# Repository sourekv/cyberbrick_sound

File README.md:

# cyberbrick_sound

Engine sound module for Bambu Lab CyberBrick RC models (first target: the truck). A small board hangs on one servo
cable from the CyberBrick receiver, gets all transmitter channels from it as serial data, and plays an engine sound
through an I2S amplifier and a speaker: idle, rpm following the throttle, a virtual gearbox, ignition with starter,
engine stop and horn. It never touches the original signal path: if the module fails, the model still drives.

**Web app for the sound sets (Chrome or Edge): https://sourekv.github.io/cyberbrick_sound/**

**Documentation, grouped by what you want to do: [`docs/README.md`](docs/README.md)**

## Status

State of 2026-11-26; what is still open: `docs/roadmap.md`.

- **The shield board works** (2026-11-21): the first assembled rev A board with a Waveshare ESP32-S3-Zero-N8R8-M and
  the firmware `engine_sets`; USB and the receiver may be connected at the same time.
- **Sound sets**: seven default sets on the module, and a web app that tests, writes and renames them, sets the volume
  and updates the firmware, over USB or Bluetooth (2026-11-22).
- **Prototype** on a breadboard in the truck before it: MAX98357A module, 40 mm 4 Ohm speaker
  in a printed 30 ml sealed box, with a speaker EQ tuned for the box (2026-11-07).
- **Channel data link works** (2026-11-06): about 27 frames per second, no checksum errors; ignition, starter,
  stop and horn from the transmitter.
- **Gearbox effects** (2026-11-08): a shift sound on every upshift; reverse is detected from the stick and does not
  shift.
- **Shield PCB**: KiCad schematic, routed board and assembly files for JLCPCB and PCBWay exist (`hardware/shield/`);
  reviewed in KiCad by a colleague of the owner on 2026-11-12 (no remarks), quoted by both services, ordered at JLCPCB on 2026-11-13 (5 assembled boards), production file and parts placement confirmed on 2026-11-14, delivered on 2026-11-20 at 12:14 (photo of the five boards: SMD parts fitted, J1/J3/J4 not yet soldered; the owner calls them "rev. 0", in the repository they are rev A).
- Which engine sound to use is the user's choice: the seven candidates became the default sets (2026-11-14).

## How it works

```
transmitter --radio--> receiver in the model --S4 servo header (S, V, G)--> sound module
```

| Where | What we added |
|---|---|
| Transmitter (CyberBrick Remote Control Transmitter Shield - XA003 XA005) | in the configuration only: the event that starts the receiver snippet by itself after power-up (moved centre of L2), and a long press of the L Shoulder Button to restart it |
| Receiver in the model (CyberBrick Remote Control Receiver Shield - XA003 XA004) | in the configuration only: our MicroPython snippet `uart_forward.py`, which sends all channels as serial data from servo header 4 (S4) to the module; the module also takes its power there |
| Sound module (ESP32-S3-Zero) | our firmware: reads the data on GPIO1 (through 1 kOhm) and makes the sound |

Bambu's firmware is unchanged on both boards. The configuration to send from the app:
`docs/cyberbrick-config/Truck_with_Engine_Sound_Data.json`. The firmware also still accepts the older variant, a
throttle-only servo pulse on PWM2. Details: `docs/controls.md`.

**Power rule:** USB and the receiver's 5 V may be connected together only through a diode in the V wire. The
breadboard prototype has a 1N5819 there since 2026-11-12 (measured: the receiver stays isolated from USB), and the
shield PCB has the OR-ing diode D2 (`docs/shield-pcb.md`). Without that diode, disconnect the V wire for flashing and
USB tests. Connect GND first and disconnect it last (`docs/bringup.md`).

## Documentation

The documents grouped by what you want to do: **[`docs/README.md`](docs/README.md)**. The full table of every document is below.

New here? **`docs/getting-started.md`** goes from the parts to the engine sound in the truck, step by step. Start with `docs/project-overview.md` (the whole project on one page) and `docs/roadmap.md` (everything still open).

**Using it: controls, wiring, configuration**

| File | What it covers |
|---|---|
| `docs/controls.md` | what we added where (transmitter, receiver, module), every transmitter control, ignition / starter / stop / horn, the receiver program and its auto-start, power-up order |
| `docs/cyberbrick-config/README.md` | the CyberBrick app configurations (`*.json`): the current channel-data config and older ones |
| `docs/cyberbrick-code/README.md` | the MicroPython snippets for the receiver (`uart_forward.py`, `blink_test.py`), test wiring and results |
| `docs/bringup.md` | bring-up of the prototype: measurements on the receiver, breadboard wiring, test order, the USB power rule |
| `docs/start-stop-horn.md` | engine start, stop and horn: the current design and the earlier notes |

**Hardware**

| File | What it covers |
|---|---|
| `docs/shield-pcb.md` | the shield PCB rev A (the board that exists): scope, schematic, routed board, mounting holes, connectors, ordering at JLCPCB, first power-up, decided and open points |
| `docs/shield-pcb-rev-b.md` | the planned next revisions (rev B prepared, not ordered; ideas such as marking the USB side of the Zero): future state, may be out of date |
| `docs/soldering.md` | soldering the hand-fitted parts of the shield (J1, J3, J4): the two ways of fitting J1, the printed stand with its insert, the procedure (one pass for J1 pins out, two for pins in) |
| `docs/shield-cost-comparison.md` | price of 5 assembled boards: PCBWay, JLCPCB with the original parts, JLCPCB with basic parts |
| `docs/speaker-measurement.md` | how the speaker response is measured (`speaker_sweep`), results bare and in the boxes, the speaker EQ |

The speaker box (OpenSCAD, Fusion 360 script, Bambu Studio project) is in `hardware/speaker_box/`; its notes are in
the header of `speaker_box.scad`.

**Sound**

| File | What it covers |
|---|---|
| `docs/sound-research.md` | engine sound research: constraints of a small speaker, approaches tried, speaker-tuned candidates, lessons |
| `docs/audio-simulation/README.md` | rendered previews of the engine sounds (`engine_lab` candidates and earlier firmware) |
| `docs/user-sounds.md` | user-changeable sound sets: the set format, what a sample must meet, the web app and its USB protocol |
| `assets/samples/LICENSE-SAMPLES.md` | origin and licence of every sound (CC0 recordings, synthesised sounds, voice prompts) |

**Plans and decisions**

| File | What it covers |
|---|---|
| `docs/roadmap.md` | everything open: next steps, checks on hardware, missing sound features, the development outlook |
| `docs/web-install-design.md` | design (not built): the first install of a new module from the web page |
| `docs/rejected-ideas.md` | ideas that were considered and dropped (shield, receiver link, sound, speaker box, USB audio), why, and what is used instead |

## Structure

A short map of every directory: `docs/contents.md`.

- `firmware/` - PlatformIO (Arduino) project; pins and all tunable constants in `firmware/include/config.h`
- `web/index.html` - the PC tool for the sound sets, also online at https://sourekv.github.io/cyberbrick_sound/ (GitHub Pages): open it in Chrome or Edge, connect the module over USB
- `tools/` - Python and C++ helpers: sound generation and rendering (`engine_lab.py`, `speaker_model.py`), header
  generators, the speaker-measurement analysis, the shield PCB generators and checks, host tests
- `assets/samples/` - the CC0 recordings and derived loops (`LICENSE-SAMPLES.md`)
- `docs/` - documentation (see above), wiring pictures, measurements (`docs/measurements/`)
- `hardware/shield/` - KiCad project of the shield board: schematic, routed PCB, manufacturing files. Versioned by
  revision letters with git tags `hw-shield-revA`, ... on the ordered files (rev A ordered; rev B, silkscreen only, is
  prepared and not ordered; `docs/shield-pcb.md`, "Revisions", and `docs/shield-pcb-rev-b.md`);
  the firmware has its own numbers and tags `v0.1.0`, ... (see "Firmware version")
- `hardware/speaker_box/` - the sealed speaker box: OpenSCAD source, Fusion 360 script, Bambu Studio project
- `hardware/solder_stand/` - printed stand for soldering the socket strips and the servo header onto the shield

## Firmware

Open `firmware/` in VS Code with the PlatformIO extension, or run `pio run -e <env> -t upload`. **A new module, step by step (the firmware, the default sets, the check): `docs/first-install.md`.**

**Firmware version**: `FW_VERSION` in `firmware/include/version.h` (now 0.1.0), raised by hand for every release,
which gets the git tag `v<version>`. At build time `firmware/version.py` adds the short hash of the commit (with
`-dirty` for uncommitted changes) and the date, so the full version reads like `0.1.0+7da2aa8`. `engine_sets`
prints it at boot (`cyberbrick_sound engine_sets 0.1.0+7da2aa8, built 2026-11-14`) and reports it to the web app
in `@info`.

| Env | What it does |
|---|---|
| `engine_sets` | **the current firmware** (first tried on the module and the web app on 2026-11-15): ignition, starter, stop and horn from the channel data, shift sound, no upshift while reversing; the sounds as sets in the data partition (`docs/user-sounds.md`): BOOT steps through them and speaks the name, sample and synth sets, fallback set compiled in; sets built by `tools/make_default_sets.py`, written with `-t uploadfs` or one by one with the web page `web/index.html` over USB or over Bluetooth (`docs/ble-link.md`: a window of 3 minutes after power-up, a spoken PIN); the page also updates the firmware and sets the overall volume |
| `engine_lab` | earlier: all seven engine-sound candidates compiled in (the BOOT button switches 1..7 and announces the name), the same controls, speaker EQ for the 30 ml box |
| `engine_demo` | the same, plays every sound through the whole rpm range by itself with a spoken announcement (no receiver needed) |
| `engine_pulse` | real-time grain synthesis (preset a_diesel6) |
| `engine`, `engine_diesel`, `engine_truck`, `engine_gears` | earlier variants: synthesised loop, CC0 diesel and truck loops with the virtual gearbox, one loop per gear |
| `engine_real` | experiment with the owner's recordings (needs a locally generated header, not in the repo) |
| `test_tone` | 440 Hz sine; checks amplifier and speaker |
| `speaker_sweep` | slow sine sweep for measuring the speaker (`docs/speaker-measurement.md`) |
| `pulse_measure`, `uart_probe` | print the servo pulse width or the receiver's channel frames to serial |

- **Virtual gearbox** (`firmware/include/gearbox.h`): the module keeps a virtual speed that follows the throttle with
  inertia and shifts through 5 gears; an effect, not a simulation. Tunable in `config.h`.
- **Status LED** on the Zero's onboard RGB LED (GPIO21): blue flash at start, red without valid data, dim green at
  rest, brightening cyan with the throttle (`STATUS_LED_*` in `config.h`).
- **Sounds**: recordings should be CC0, but we had to make some concessions (CC BY with the author credited is accepted, decided 2026-11-02; a few origins cannot be fully verified); everything else is synthesised. Each sound keeps its own licence: the table in `assets/samples/LICENSE-SAMPLES.md` lists source, author, licence, credit and the doubts. Why the sound is built this way:
  `docs/sound-research.md`.

## Wiring

With the shield board there is only the servo cable (J1 to S4) and the speaker: `docs/getting-started.md`, with a photo.
Below is the wiring of the breadboard prototype that came before it.

*The breadboard prototype with the receiver, battery, motor and speaker box (2026-11-12).*

Source: `docs/wiring-current.svg`. Earlier development stages (module on USB, only signal and GND from the receiver;
then power from the servo port): `docs/wiring-overview.png`, `docs/wiring-stage2.png`, `docs/wiring-test-tone.png`.
Pins, test order and measurements: `docs/bringup.md`.

**Note on old version strings:** on 2026-11-24 the git history was rewritten before the repository was made public, so every commit hash changed. Version strings that the module reported before that date (in `docs/ble-link.md`, `docs/shield-pcb.md` and `docs/bringup.md`, for example `0.1.0+7890eb9`) are the hashes of the old history and no longer exist in the repository; the dates next to them identify the commits.

## Licence

The project has three licences, by kind of work:

| What | Licence | Where |
|---|---|---|
| Software: firmware, web app, tools (and the sounds the project synthesises from its own code) | **GNU GPL v3 or later** | `LICENSE` |
| Hardware design files: the shield board (KiCad), the printed solder stand and the speaker box (OpenSCAD) | **CERN-OHL-S v2** (strongly reciprocal open hardware licence) | `hardware/LICENSE`, `hardware/README.md` |
| Documentation and its pictures (`docs/`) | **CC BY-SA 4.0** | `docs/LICENSE` |

The third-party sounds in `assets/samples/` keep their own licences, listed file by file in `assets/samples/LICENSE-SAMPLES.md`.

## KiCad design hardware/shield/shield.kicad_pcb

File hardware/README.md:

# Hardware of cyberbrick_sound

The shield board (`shield/`, KiCad), the printed solder stand (`solder_stand/`, OpenSCAD) and the speaker box (`speaker_box/`) are Open Hardware.

**Licence: CERN Open Hardware Licence Version 2 - Strongly Reciprocal (CERN-OHL-S-2.0)**, full text in `LICENSE` in this folder.

This documentation describes Open Hardware and is licensed under the CERN-OHL-S v2. You may redistribute and modify this documentation and make products using it under the terms of the CERN-OHL-S v2 (https://ohwr.org/cern_ohl_s_v2.txt). This documentation is distributed WITHOUT ANY EXPRESS OR IMPLIED WARRANTY, INCLUDING OF MERCHANTABILITY, SATISFACTORY QUALITY AND FITNESS FOR A PARTICULAR PURPOSE. Please see the CERN-OHL-S v2 for applicable conditions.

Source location: https://github.com/sourekv/cyberbrick_sound/tree/main/hardware

Parts that come from others (for example the KiCad symbol and footprint libraries, CC-BY-SA 4.0 with the KiCad libraries exception) keep their own licences.

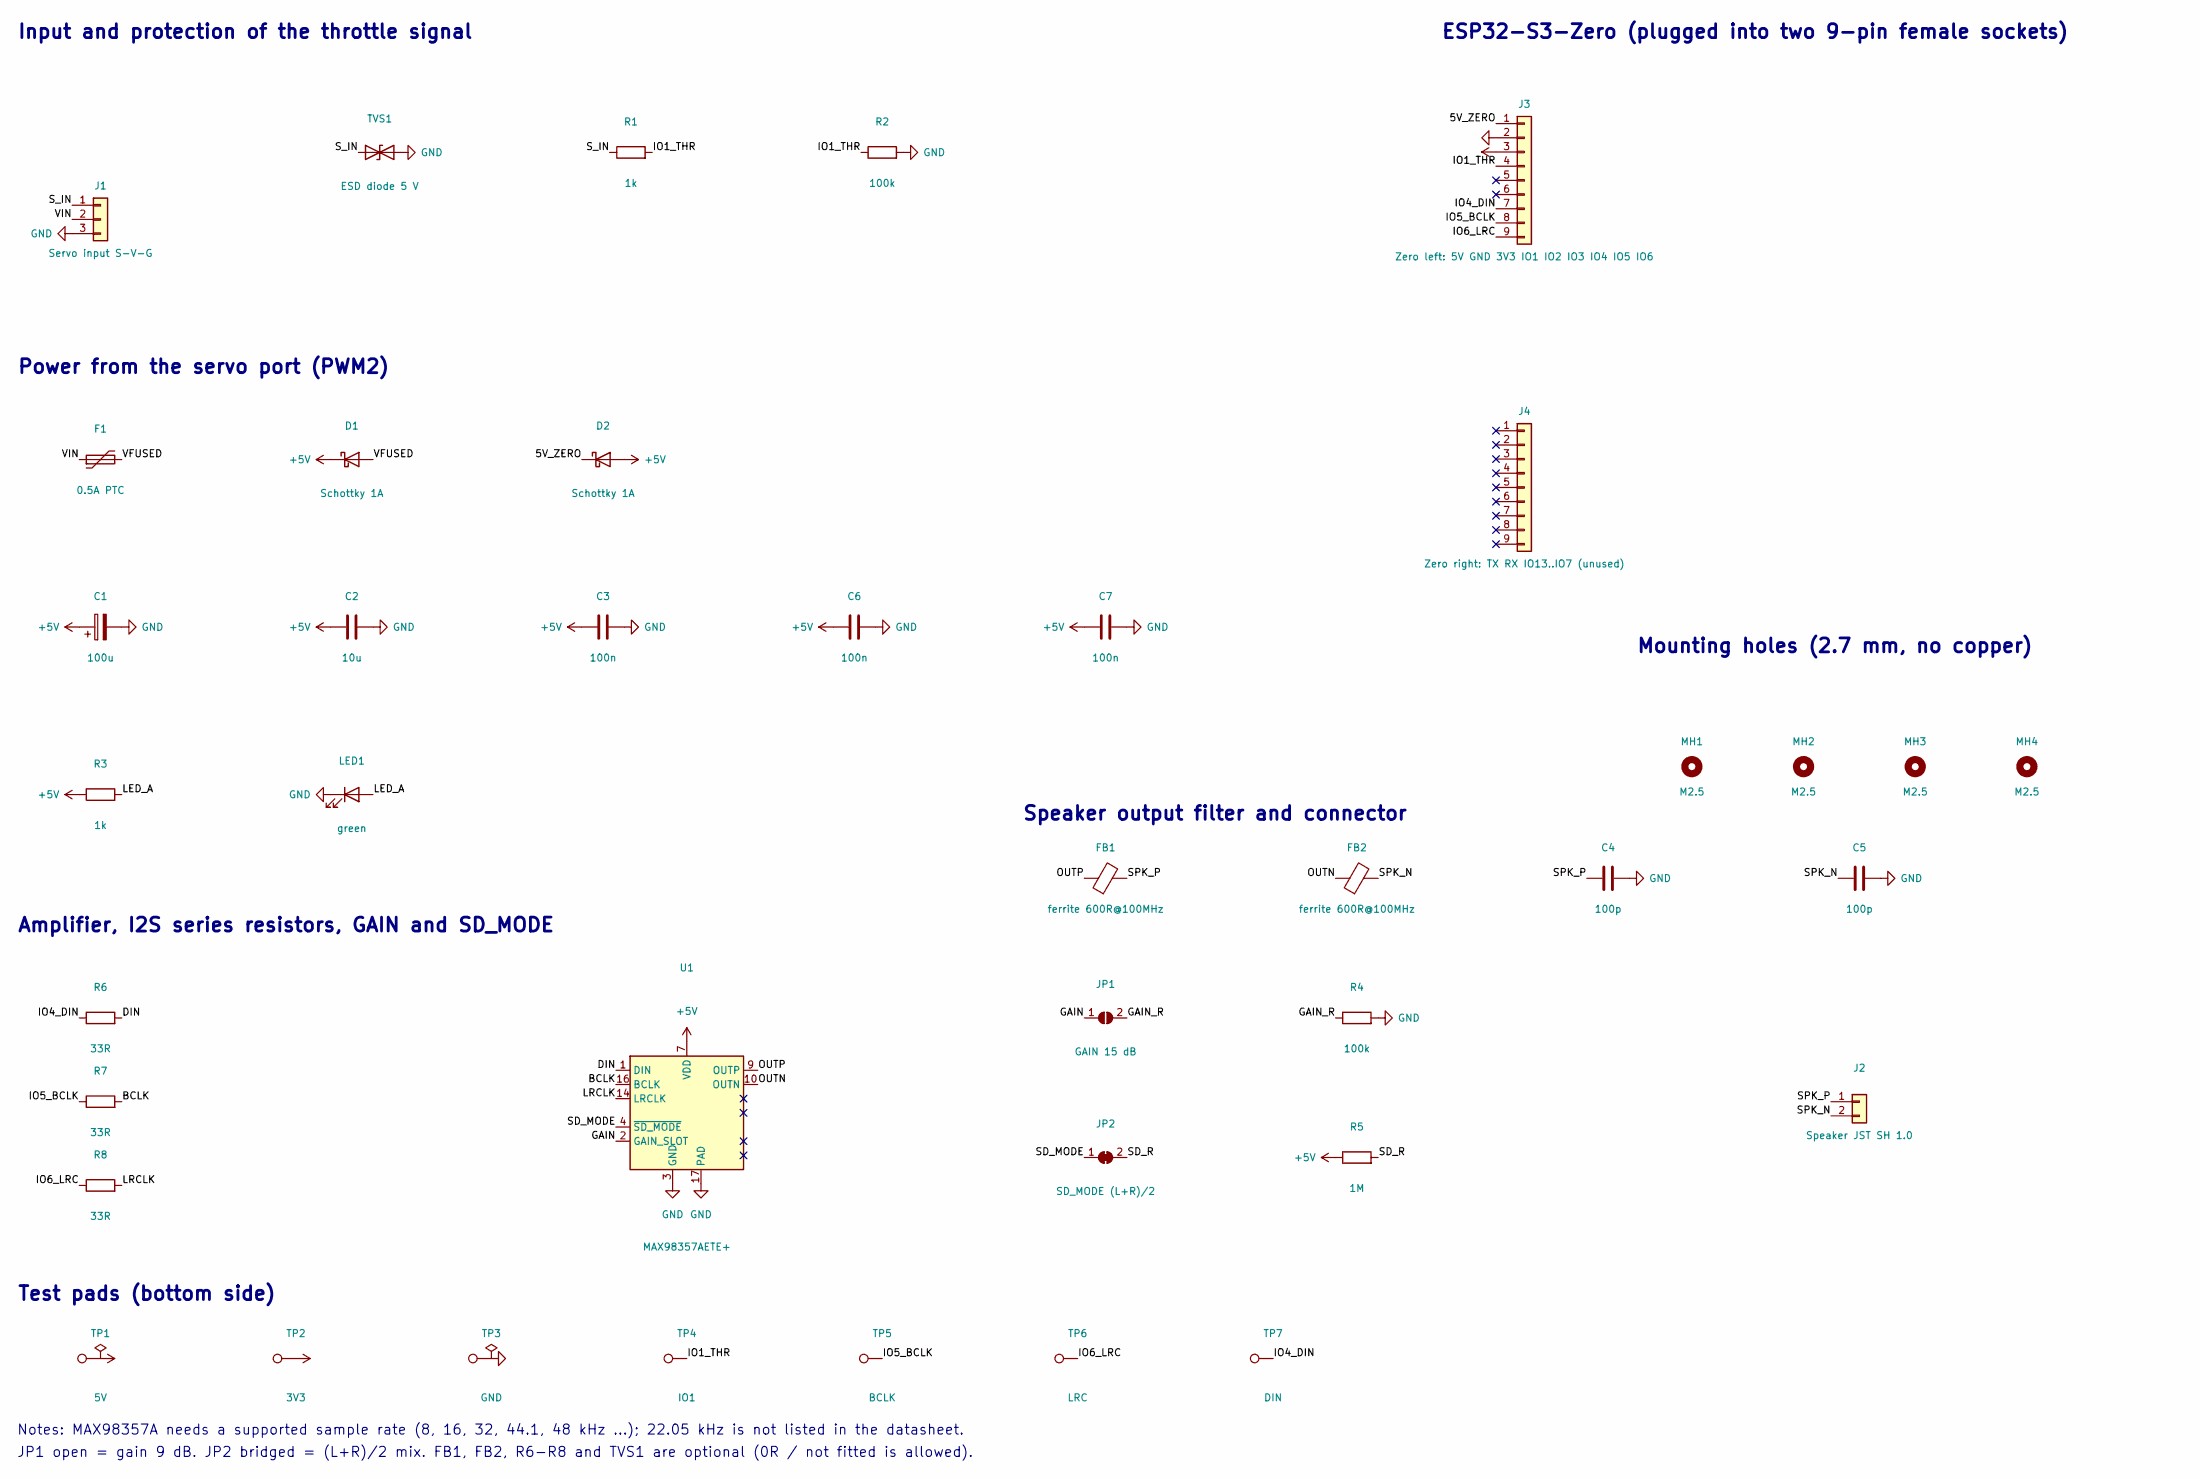
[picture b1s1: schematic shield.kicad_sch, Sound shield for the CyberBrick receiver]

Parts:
C1: 100u; CP_EIA-6032-28_Kemet-C
C2: 10u; C_0805_2012Metric
C3, C6, C7: 100n; C_0603_1608Metric
C4, C5: 100p; C_0603_1608Metric
D1, D2: Schottky 1A; D_SOD-123
F1: 0.5A PTC; Fuse_1206_3216Metric
FB1, FB2: ferrite 600R@100MHz; L_0603_1608Metric
J1: Servo input S-V-G; PinHeader_1x03_P2.54mm_Horizontal
J2: Speaker JST SH 1.0; JST_SH_SM02B-SRSS-TB_1x02-1MP_P1.00mm_Horizontal
J3: Zero left: 5V GND 3V3 IO1 IO2 IO3 IO4 IO5 IO6; PinSocket_1x09_P2.54mm_Vertical
J4: Zero right: TX RX IO13..IO7 (unused); PinSocket_1x09_P2.54mm_Vertical
JP1: GAIN 15 dB; SolderJumper-2_P1.3mm_Open_Pad1.0x1.5mm
JP2: SD_MODE (L+R)/2; SolderJumper-2_P1.3mm_Bridged_Pad1.0x1.5mm
LED1: green; LED_0603_1608Metric
MH1, MH2, MH3, MH4: M2.5; MountingHole_2.7mm_M2.5
R1, R3: 1k; R_0603_1608Metric
R2, R4: 100k; R_0603_1608Metric
R5: 1M; R_0603_1608Metric
R6, R7, R8: 33R; R_0603_1608Metric
TP1: 5V; TestPoint_Pad_D1.0mm
TP2: 3V3; TestPoint_Pad_D1.0mm
TP3: GND; TestPoint_Pad_D1.0mm
TP4: IO1; TestPoint_Pad_D1.0mm
TP5: BCLK; TestPoint_Pad_D1.0mm
TP6: LRC; TestPoint_Pad_D1.0mm
TP7: DIN; TestPoint_Pad_D1.0mm
TVS1: ESD diode 5 V; D_SOD-323
U1: MAX98357AETE+; TQFN-16-1EP_3x3mm_P0.5mm_EP1.23x1.23mm

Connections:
5V_ZERO: D2.1 (K), J3.1
+3V3: J3.3, TP2.1
+5V: C1.1, C2.1, C3.1, C6.1, C7.1, D1.1 (K), D2.2 (A), R3.1, R5.1, TP1.1, U1.7 (VDD), U1.8 (VDD)
BCLK: R7.2, U1.16 (BCLK)
DIN: R6.2, U1.1 (DIN)
GAIN: JP1.1 (A), U1.2 (GAIN_SLOT)
GAIN_R: JP1.2 (B), R4.1
GND: C1.2, C2.2, C3.2, C4.2, C5.2, C6.2, C7.2, J1.3, J3.2, LED1.1 (K), R2.2, R4.2, TP3.1, TVS1.2 (A2), U1.3 (GND), U1.11 (GND), U1.15 (GND), U1.17 (PAD)
IO1_THR: J3.4, R1.2, R2.1, TP4.1
IO4_DIN: J3.7, R6.1, TP7.1
IO5_BCLK: J3.8, R7.1, TP5.1
IO6_LRC: J3.9, R8.1, TP6.1
LED_A: LED1.2 (A), R3.2
LRCLK: R8.2, U1.14 (LRCLK)
OUTN: FB2.1, U1.10 (OUTN)
OUTP: FB1.1, U1.9 (OUTP)
SD_MODE: JP2.1 (A), U1.4 (~SD_MODE)
SD_R: JP2.2 (B), R5.2
SPK_N: C5.1, FB2.2, J2.2
SPK_P: C4.1, FB1.2, J2.1
S_IN: J1.1, R1.1, TVS1.1 (A1)
VFUSED: D1.2 (A), F1.2
VIN: F1.1, J1.2

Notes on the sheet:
Input and protection of the throttle signal
Power from the servo port (PWM2)
ESP32-S3-Zero (plugged into two 9-pin female sockets)
Amplifier, I2S series resistors, GAIN and SD_MODE
Speaker output filter and connector
Test pads (bottom side)
Mounting holes (2.7 mm, no copper)
Notes: MAX98357A needs a supported sample rate (8, 16, 32, 44.1, 48 kHz ...); 22.05 kHz is not listed in the datasheet.
JP1 open = gain 9 dB. JP2 bridged = (L+R)/2 mix. FB1, FB2, R6-R8 and TVS1 are optional (0R / not fitted is allowed).

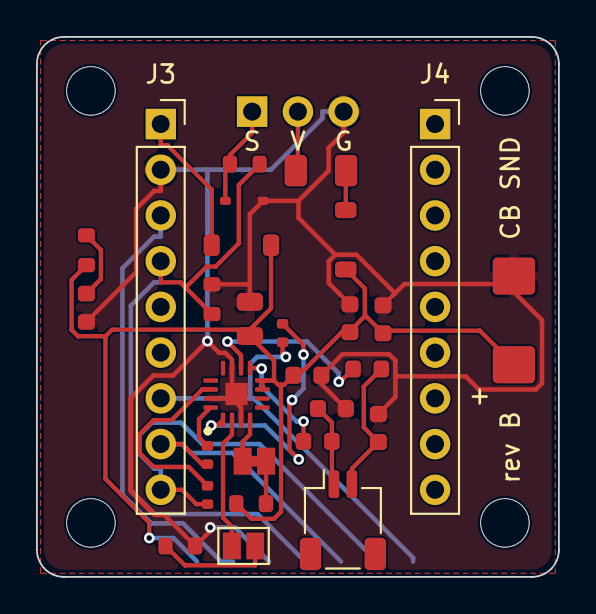
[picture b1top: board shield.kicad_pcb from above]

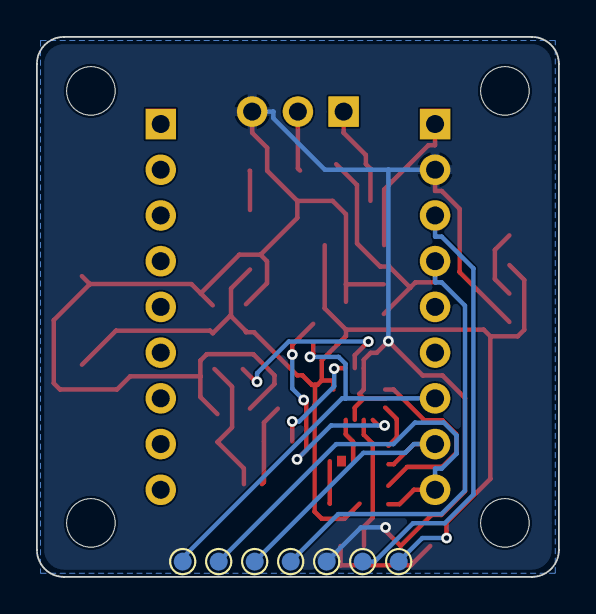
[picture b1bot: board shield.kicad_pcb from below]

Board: 2 copper layers, 29.0 x 30.0 mm, 40 parts (7 on the bottom side), 23 nets.

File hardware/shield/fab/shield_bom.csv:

Designators,Qty,Value,Footprint,LCSC,Note
C1,1,100u,CP_EIA-6032-28_Kemet-C,C8649,Bulk capacitor
C2,1,10u,C_0805_2012Metric,C15850,Amplifier supply decoupling
C3,1,100n,C_0603_1608Metric,C1591,Amplifier supply decoupling
"C4,C5",2,100p,C_0603_1608Metric,C14858,EMI capacitor at the speaker connector
"C6,C7",2,100n,C_0603_1608Metric,C1591,General decoupling
D1,1,Schottky 1A,D_SOD-123,C8598,Reverse-polarity protection
D2,1,Schottky 1A,D_SOD-123,C8598,OR-ing: servo 5 V and USB 5 V can both be connected
F1,1,0.5A PTC,Fuse_1206_3216Metric,C43379,Resettable fuse
"FB1,FB2",2,ferrite 600R@100MHz,L_0603_1608Metric,C85833,Speaker output filter (can be 0R)
J1,1,Servo input S-V-G,PinHeader_1x03_P2.54mm_Horizontal,hand-soldered,"Right-angle male header, servo cable to the receiver's S4 header (channel data and 5 V)"
J2,1,Speaker JST SH 1.0,JST_SH_SM02B-SRSS-TB_1x02-1MP_P1.00mm_Horizontal,C160402,"Speaker connector, same type as the CyberBrick motor ports"
J3,1,Zero left: 5V GND 3V3 IO1 IO2 IO3 IO4 IO5 IO6,PinSocket_1x09_P2.54mm_Vertical,hand-soldered,Socket for the left pin row of the ESP32-S3-Zero
J4,1,Zero right: TX RX IO13..IO7 (unused),PinSocket_1x09_P2.54mm_Vertical,hand-soldered,Socket for the right pin row of the ESP32-S3-Zero (no signals used)
JP1,1,GAIN 15 dB,SolderJumper-2_P1.3mm_Open_Pad1.0x1.5mm,,Open: GAIN floating = 9 dB. Bridged: 100k to ground = 15 dB
JP2,1,SD_MODE (L+R)/2,SolderJumper-2_P1.3mm_Bridged_Pad1.0x1.5mm,,Bridged by default; cut open = amplifier in shutdown
LED1,1,green,LED_0603_1608Metric,C12624,Power LED
R1,1,1k,R_0603_1608Metric,C21190,Series resistor to GPIO1
R2,1,100k,R_0603_1608Metric,C25803,Pull-down on GPIO1
R3,1,1k,R_0603_1608Metric,C21190,Power LED resistor (about 3 mA)
R4,1,100k,R_0603_1608Metric,C25803,GAIN resistor
R5,1,1M,R_0603_1608Metric,C22935,SD_MODE pull-up: with the internal 100k pull-down gives (L+R)/2
R6,1,33R,R_0402_1005Metric,C25105,Series resistor DIN (can be 0R)
R7,1,33R,R_0402_1005Metric,C25105,Series resistor BCLK (can be 0R)
R8,1,33R,R_0402_1005Metric,C25105,Series resistor LRC (can be 0R)
TVS1,1,ESD diode 5 V,D_SOD-323,C19224,ESD protection of the data input
U1,1,MAX98357AETE+,TQFN-16-1EP_3x3mm_P0.5mm_EP1.23x1.23mm,C910544,I2S class-D amplifier
